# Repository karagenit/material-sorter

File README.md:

# Material Sorter

Sorting Spare Materials (Bolts, Nuts, Washers, etc) - DE Final Project.

## Features

Using a Raspberry Pi Camera, we can categorize bolts according to their length and width. Each type is assigned a bin ID#, which is sent to an Arduino via serial. The Arduino controls a servo to position the appropriate bin for the bolt to be placed into, and displays the ID# on a Seven Segment display.

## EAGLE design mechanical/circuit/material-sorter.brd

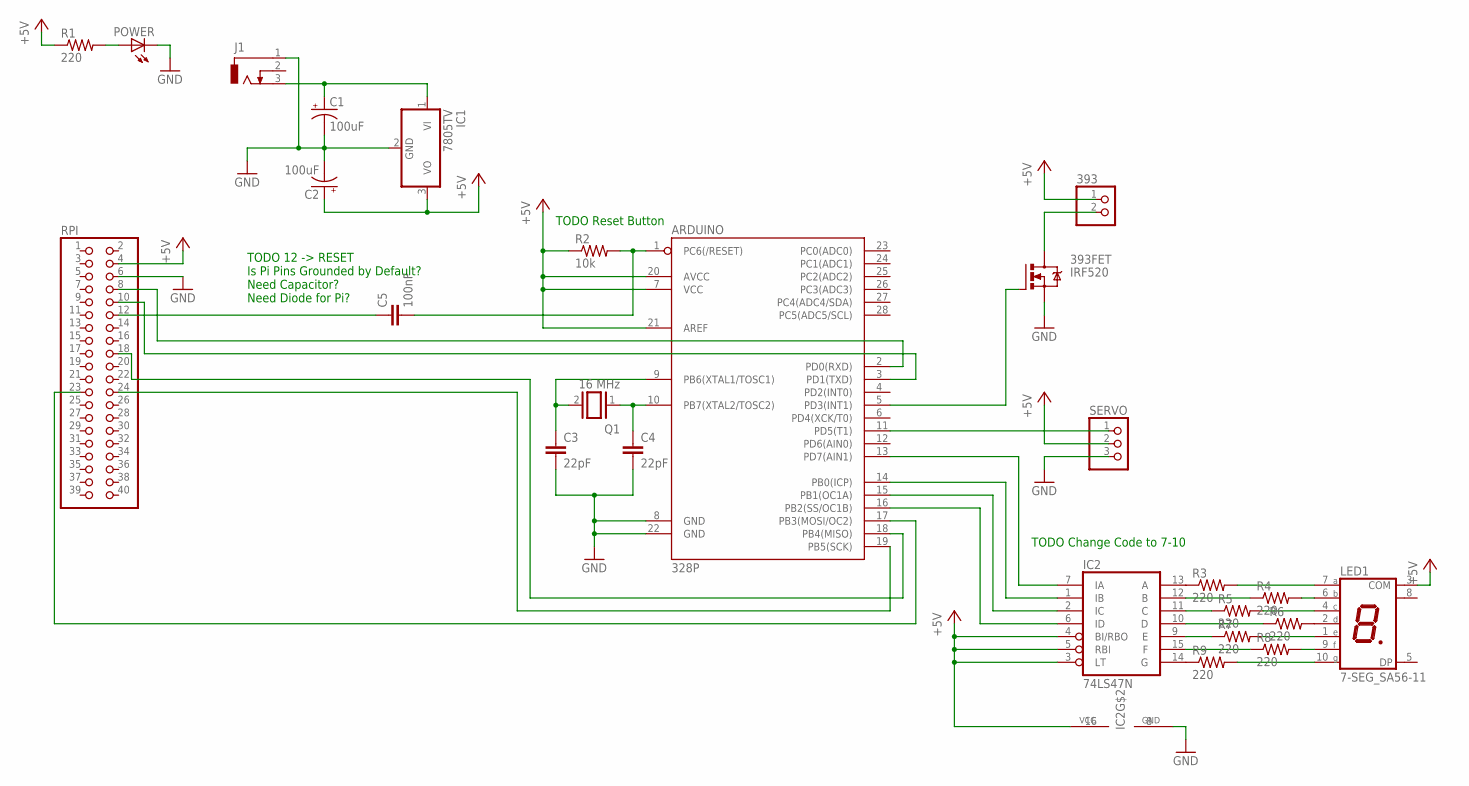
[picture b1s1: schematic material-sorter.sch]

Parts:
393: PINHD-1X2; 1X02
393FET: IRF520; TO220BV
ARDUINO: 328P; DIP28
C1, C2: 100uF; E2,5-5
C3, C4: 22pF; C2.5-5
C5: 100nF; C2.5-5
IC1: 7805TV; TO220V
IC2: 74LS47N; DIL16
J1: DCJ0303
LED1: 7-SEG_SA56-11; SA56-11
POWER: LED5MM
Q1: 16 MHz; QS
R1, R3, R4, R5, R6, R7, R8, R9: 220; 0207/2V
R2: 10k; 0207/2V
RPI: PINHD-2X20; 2X20
SERVO: PINHD-1X3; 1X03

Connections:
+5V: 393.1, ARDUINO.7 (VCC), ARDUINO.20 (AVCC), ARDUINO.21 (AREF), C2.+, IC1.3 (VO), IC2.3 (LT), IC2.4 (BI/RBO), IC2.5 (RBI), IC2.16 (VCC), LED1.3 (COM), R1.1, R2.1, RPI.4, SERVO.2
GND: 393FET.S, ARDUINO.8 (GND), ARDUINO.22 (GND), C1.-, C2.-, C3.2, C4.2, IC1.2 (GND), IC2.8 (GND), J1.1, POWER.K (C), RPI.6, SERVO.3
unnamed: ARDUINO.2 (PD0(RXD)), RPI.8
unnamed: ARDUINO.3 (PD1(TXD)), RPI.10
unnamed: ARDUINO.1 (PC6(/RESET)), C5.2, R2.2
unnamed: C1.+, IC1.1 (VI), J1.3
unnamed: ARDUINO.19 (PB5(SCK)), RPI.24
unnamed: POWER.A, R1.2
unnamed: ARDUINO.17 (PB3(MOSI/OC2)), RPI.23
unnamed: ARDUINO.18 (PB4(MISO)), RPI.18
unnamed: ARDUINO.10 (PB7(XTAL2/TOSC2)), C4.1, Q1.1
unnamed: ARDUINO.9 (PB6(XTAL1/TOSC1)), C3.1, Q1.2
unnamed: ARDUINO.11 (PD5(T1)), SERVO.1
unnamed: ARDUINO.13 (PD7(AIN1)), IC2.7 (IA)
unnamed: 393FET.G, ARDUINO.5 (PD3(INT1))
unnamed: 393.2, 393FET.D
unnamed: ARDUINO.14 (PB0(ICP)), IC2.1 (IB)
unnamed: ARDUINO.15 (PB1(OC1A)), IC2.2 (IC)
unnamed: ARDUINO.16 (PB2(SS/OC1B)), IC2.6 (ID)
unnamed: C5.1, RPI.12
unnamed: IC2.13 (A), R3.1
unnamed: LED1.2 (D), R6.2
unnamed: IC2.14 (G), R9.1
unnamed: LED1.7 (A), R3.2
unnamed: IC2.12 (B), R4.1
unnamed: LED1.6 (B), R4.2
unnamed: LED1.4 (C), R5.2
unnamed: LED1.1 (E), R7.2
unnamed: LED1.9 (F), R8.2
unnamed: LED1.10 (G), R9.2
unnamed: IC2.11 (C), R5.1
unnamed: IC2.10 (D), R6.1
unnamed: IC2.9 (E), R7.1
unnamed: IC2.15 (F), R8.1

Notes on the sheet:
TODO 12 -> RESET Is Pi Pins Grounded by Default? Need Capacitor? Need Diode for Pi?
TODO Reset Button
TODO Change Code to 7-10

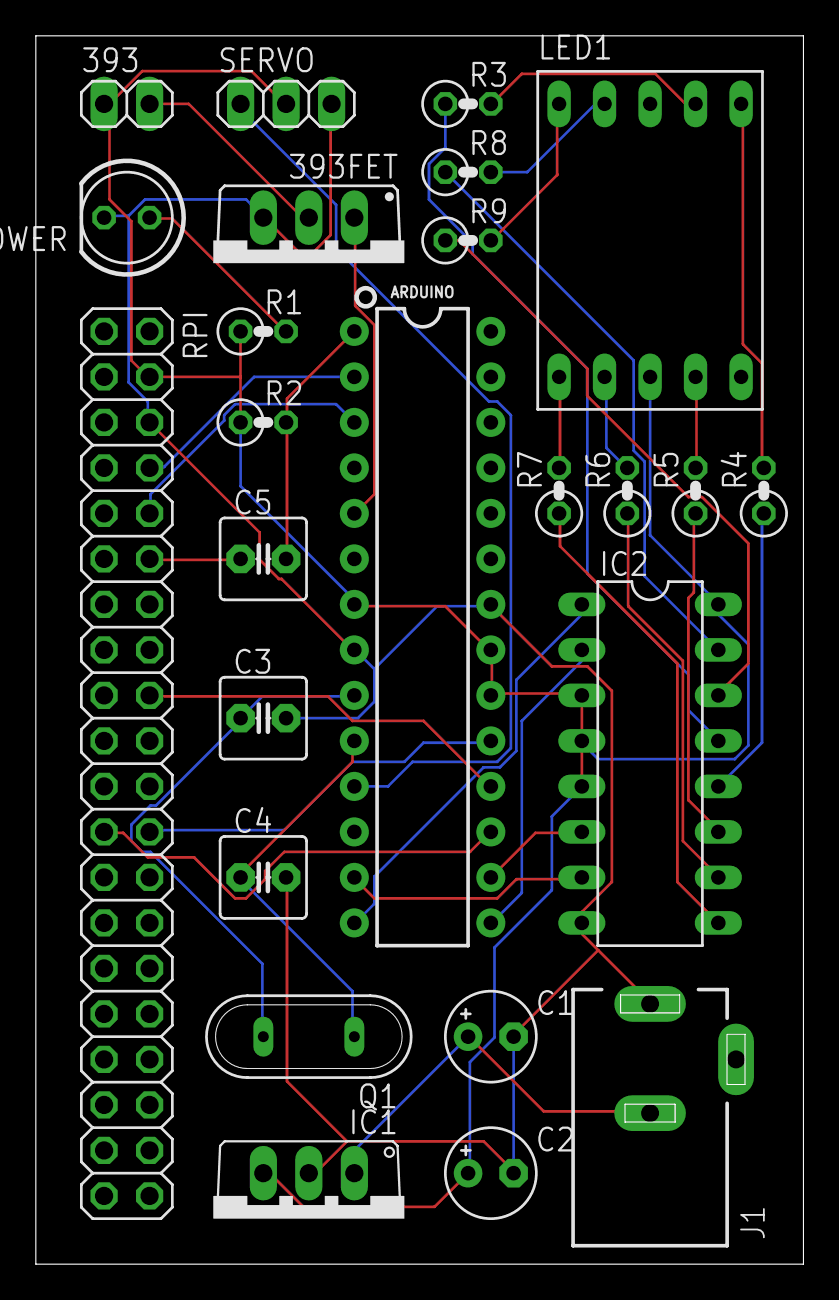
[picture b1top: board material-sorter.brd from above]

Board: 2 copper layers, 42.9 x 68.6 mm, 25 parts (0 on the bottom side), 34 nets.

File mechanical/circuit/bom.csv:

"Part";"Value";"Device";"Package";"Description";"MF";"MPN";"OC_FARNELL";"OC_NEWARK";"PROD_ID";"VALUE";
"393";"";"PINHD-1X2";"1X02";"PIN HEADER";"";"";"";"";"";"";
"393FET";"IRF520";"IRF520";"TO220BV";"HEXFET Power MOSFET";"";"";"";"";"";"";
"ARDUINO";"328P";"ATMEGA328P_PDIP";"DIP28";"Atmel 328P";"";"";"";"";"IC-09136";"328P";
"C1";"100uF";"CPOL-USE2.5-5";"E2,5-5";"POLARIZED CAPACITOR, American symbol";"";"";"";"";"";"";
"C2";"100uF";"CPOL-USE2.5-5";"E2,5-5";"POLARIZED CAPACITOR, American symbol";"";"";"";"";"";"";
"C3";"22pF";"C2.5/5";"C2.5-5";"CAPACITOR";"";"";"";"";"";"";
"C4";"22pF";"C2.5/5";"C2.5-5";"CAPACITOR";"";"";"";"";"";"";
"C5";"100nF";"C2.5/5";"C2.5-5";"CAPACITOR";"";"";"";"";"";"";
"IC1";"7805TV";"7805TV";"TO220V";"Positive VOLTAGE REGULATOR";"";"";"";"";"";"";
"IC2";"74LS47N";"74LS47N";"DIL16";"BCD to seven segment DECODER/DRIVER";"";"";"";"";"";"";
"J1";"";"DCJ0303";"DCJ0303";"DC POWER JACK";"";"";"unknown";"unknown";"";"";
"LED1";"7-SEG_SA56-11";"7-SEG_SA56-11";"SA56-11";"Kingbright 14.2mm (0.56 INCH) SINGLE DIGIT NUMERIC DUISPLAY";"";"";"unknown";"unknown";"";"";
"POWER";"";"LED5MM";"LED5MM";"LED";"";"";"";"";"";"";
"Q1";"16 MHz";"XTAL/S";"QS";"CRYSTAL";"";"";"";"";"";"";
"R1";"220";"R-US_0207/2V";"0207/2V";"RESISTOR, American symbol";"";"";"";"";"";"";
"R2";"10k";"R-US_0207/2V";"0207/2V";"RESISTOR, American symbol";"";"";"";"";"";"";
"R3";"220";"R-US_0207/2V";"0207/2V";"RESISTOR, American symbol";"";"";"";"";"";"";
"R4";"220";"R-US_0207/2V";"0207/2V";"RESISTOR, American symbol";"";"";"";"";"";"";
"R5";"220";"R-US_0207/2V";"0207/2V";"RESISTOR, American symbol";"";"";"";"";"";"";
"R6";"220";"R-US_0207/2V";"0207/2V";"RESISTOR, American symbol";"";"";"";"";"";"";
"R7";"220";"R-US_0207/2V";"0207/2V";"RESISTOR, American symbol";"";"";"";"";"";"";
"R8";"220";"R-US_0207/2V";"0207/2V";"RESISTOR, American symbol";"";"";"";"";"";"";
"R9";"220";"R-US_0207/2V";"0207/2V";"RESISTOR, American symbol";"";"";"";"";"";"";
"RPI";"";"PINHD-2X20";"2X20";"PIN HEADER";"";"";"";"";"";"";
"SERVO";"";"PINHD-1X3";"1X03";"PIN HEADER";"";"";"";"";"";"";

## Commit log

2017-09-01 Add Directories
2017-09-01 Add Initial Arduino File
2017-09-04 Add Arduino Enum/Structs
2017-09-04 Add Java README
2017-09-04 Add Belt & Bin Arrays
2017-09-04 Update Defines
2017-09-05 Add Skeleton Code
2017-09-05 Add Rotate Belt
2017-09-05 Fix No Return Warning
2017-09-05 Complete Add Material Function
2017-09-05 Add Struct Comparator
2017-09-05 Add Push Bin/Materials
2017-09-05 Move Struct/Enum to Header
2018-02-06 Remove Java Directory
2018-02-06 Add Python Directory
2018-03-19 Add Python Files
2018-04-12 Rename IO File to Fix Import Errors
2018-04-12 Add Git Ignore
2018-04-12 Update Git Ignore
2018-04-12 Change Import Style
2018-04-12 Add Await Function
2018-04-12 Add OpenCV Import
2018-04-12 Add Requirements File
2018-04-12 Display Image
2018-04-12 Add Color Range Filtering
2018-04-12 Cleanup Functions
2018-04-12 Add Vision Analysis and Bolt Class
2018-04-12 Overlay Contours
2018-04-12 Add Mild Erosion Filter
2018-04-15 Add Vision Constants
2018-04-15 Process Bolt Image
2018-04-15 Tune Image Processing
2018-04-15 Find Bounding Rectangle
2018-04-15 Add Length/Width Calculation
2018-04-15 Add Pixel to Inch Conversion Helper
2018-04-15 Add Arduino Send Method
2018-04-15 Implement == in Bolt
2018-04-15 Update Requirements
2018-04-15 Add Serial Communication Framework
2018-04-16 Move Requirements File
2018-04-16 Move Bolt Image
2018-04-16 Enable Test Mode Flag
2018-04-16 Update Documentation
2018-04-16 Add Test Arduino File
2018-04-20 Add Camera Reading Code
2018-04-20 Add Global Declarations
2018-04-20 Tune Vision
2018-04-20 Find Best Bounding Rectangle
2018-04-20 Handle Ctrl-C & Exits
2018-04-20 Fix Capture Buffer Exception
2018-04-20 Capture in Loop
2018-04-20 Move Function Calls
2018-04-20 Set Camera Resolution
2018-04-20 Tune Vision & Don't Display Debug
2018-04-20 Setup Pi to run with Arduino
2018-04-20 Fix Arduino Serial Code
2018-04-20 Reduce Bin Length Resolution
2018-04-20 Change Camera Resolution
    Closes #4
2018-04-20 Add Arduino Test Script
2018-05-04 Add Arduino Servo Control
2018-05-04 Blink Based on Bin #
2018-05-04 Display Bin on 7 Segment Display
2018-05-14 Add Working Servo Control Code
2018-05-16 Add Turntable Motor to Arduino
2018-05-16 Add Circuit Documentation
2018-05-16 Add Arduino Makefile
2018-05-16 Add Avrdude to Makefile
2018-05-17 Add Datasheets/Files
2018-05-17 Add Eagle Files
2018-05-17 Add Power Budget
2018-05-22 Remove Board Files
2018-05-22 Add PCB Submodule
    Closes #20

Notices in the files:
parts and their libraries:
SparkFun-IC-Microcontroller: Licensing: Creative Commons ShareAlike 4.0 International - https://creativecommons.org/licenses/by-sa/4.0
